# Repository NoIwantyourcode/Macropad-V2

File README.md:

# Macropad V2
An upgraded Macropad that features 9 keys and uses matricies to wire them up ensuring efficient wiring and use of pins, The keys are wired in a row's of 3 and columns of 3, This allows only 6 pins to be used

# Why I made this?
I made this because I wamted to iterate and improve on my last macropad where I messed up while putting in the screws

# Pictures

# Schematics

# PCB design

# Rendered PCB

# Assembled View

# Assembled picture

# Demo video link

here [https://youtube.com/shorts/qXaWAsnLh1U](https://youtube.com/shorts/qXaWAsnLh1U)

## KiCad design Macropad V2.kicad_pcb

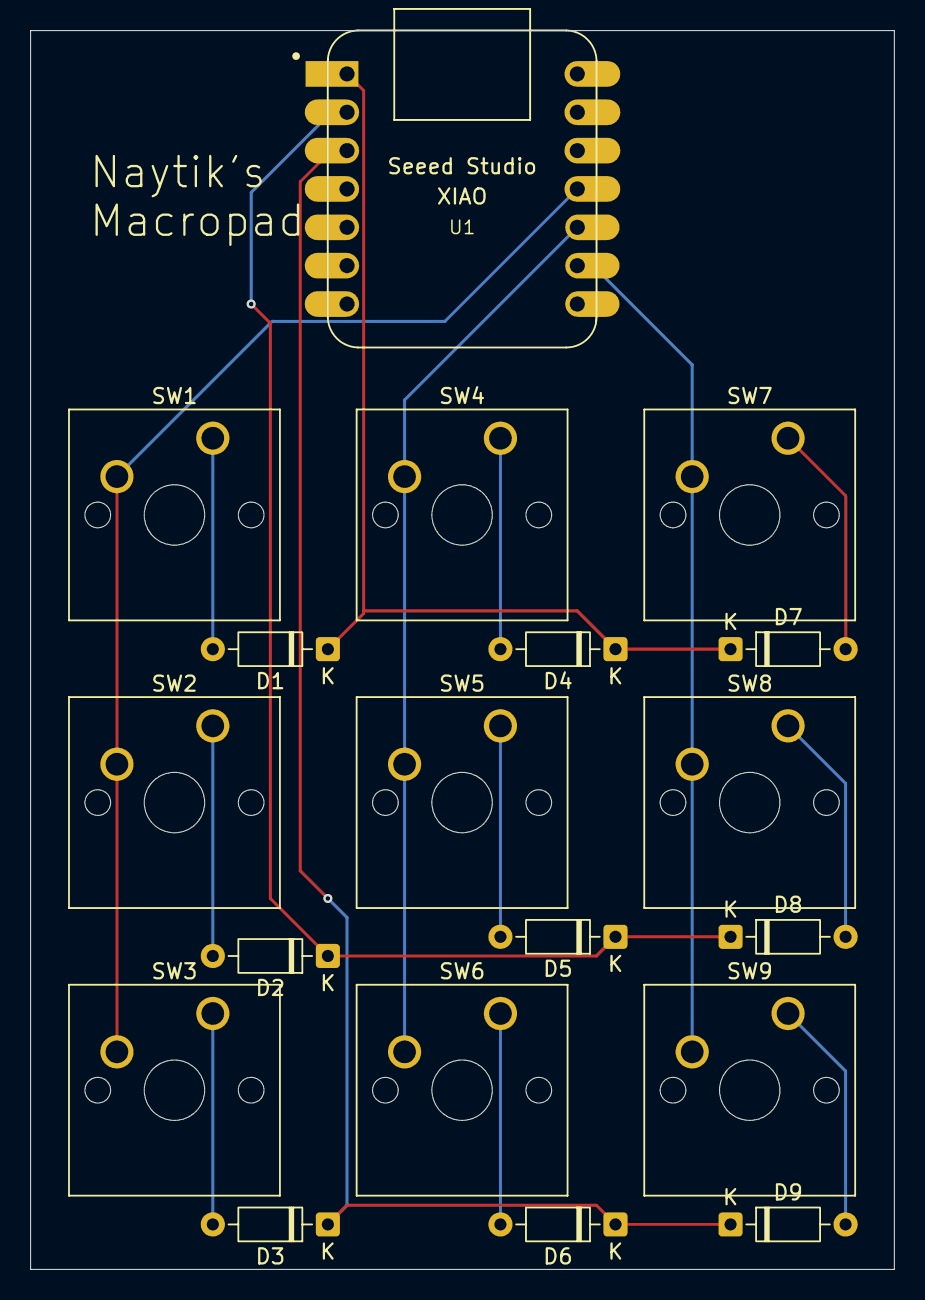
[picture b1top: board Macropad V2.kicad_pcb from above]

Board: 2 copper layers, 57.2 x 82.0 mm, 19 parts (0 on the bottom side), 15 nets.

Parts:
D1, D2, D3, D4, D5, D6, D7, D8, D9: 1N4148; D_DO-35_SOD27_P7.62mm_Horizontal
SW1, SW2, SW3, SW4, SW5, SW6, SW7, SW8, SW9: SW_Push; SW_Cherry_MX_1.00u_PCB
U1: MOUDLE-SEEEDUINO-XIAO; XIAO-Generic-Hybrid-14P-2.54-21X17.8MM

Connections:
/Col1: SW1.2, SW2.2, SW3.2, U1.11 (PA6_A10_D10_MOSI)
/Col2: SW4.2, SW5.2, SW6.2, U1.10 (PA5_A9_D9_MISO)
/Col3: SW7.2, SW8.2, SW9.2, U1.9 (PA7_A8_D8_SCK)
/Row1: D1.1 (K), D4.1 (K), D7.1 (K), U1.1 (PA02_A0_D0)
/Row2: D2.1 (K), D5.1 (K), D8.1 (K), U1.2 (PA4_A1_D1)
/Row3: D3.1 (K), D6.1 (K), D9.1 (K), U1.3 (PA10_A2_D2)
unnamed: D1.2 (A), SW1.1
unnamed: D2.2 (A), SW2.1
unnamed: D3.2 (A), SW3.1
unnamed: D4.2 (A), SW4.1
unnamed: D5.2 (A), SW5.1
unnamed: D6.2 (A), SW6.1
unnamed: D7.2 (A), SW7.1
unnamed: D8.2 (A), SW8.1
unnamed: D9.2 (A), SW9.1

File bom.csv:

Designator,Footprint,Quantity,Value,LCSC Part #
"D1, D2, D3, D4, D5, D6, D7, D8, D9",D_DO-35_SOD27_P7.62mm_Horizontal,9,1N4148,
"SW1, SW2, SW3, SW4, SW5, SW6, SW7, SW8, SW9",SW_Cherry_MX_1.00u_PCB,9,SW_Push,
U1,XIAO-Generic-Hybrid-14P-2.54-21X17.8MM,1,MOUDLE-SEEEDUINO-XIAO,

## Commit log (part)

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2026-06-03 added PCB art!
2026-06-03 Update README with details on key configuration
    Clarified the number of keys and wiring configuration in the README.
2026-06-03 Add journal entries for June 3rd, 2026
    Documented the completion of schematics, PCB routing, and case design with images.
2026-06-03 added case files and production files
2026-06-03 added bom and firmware
